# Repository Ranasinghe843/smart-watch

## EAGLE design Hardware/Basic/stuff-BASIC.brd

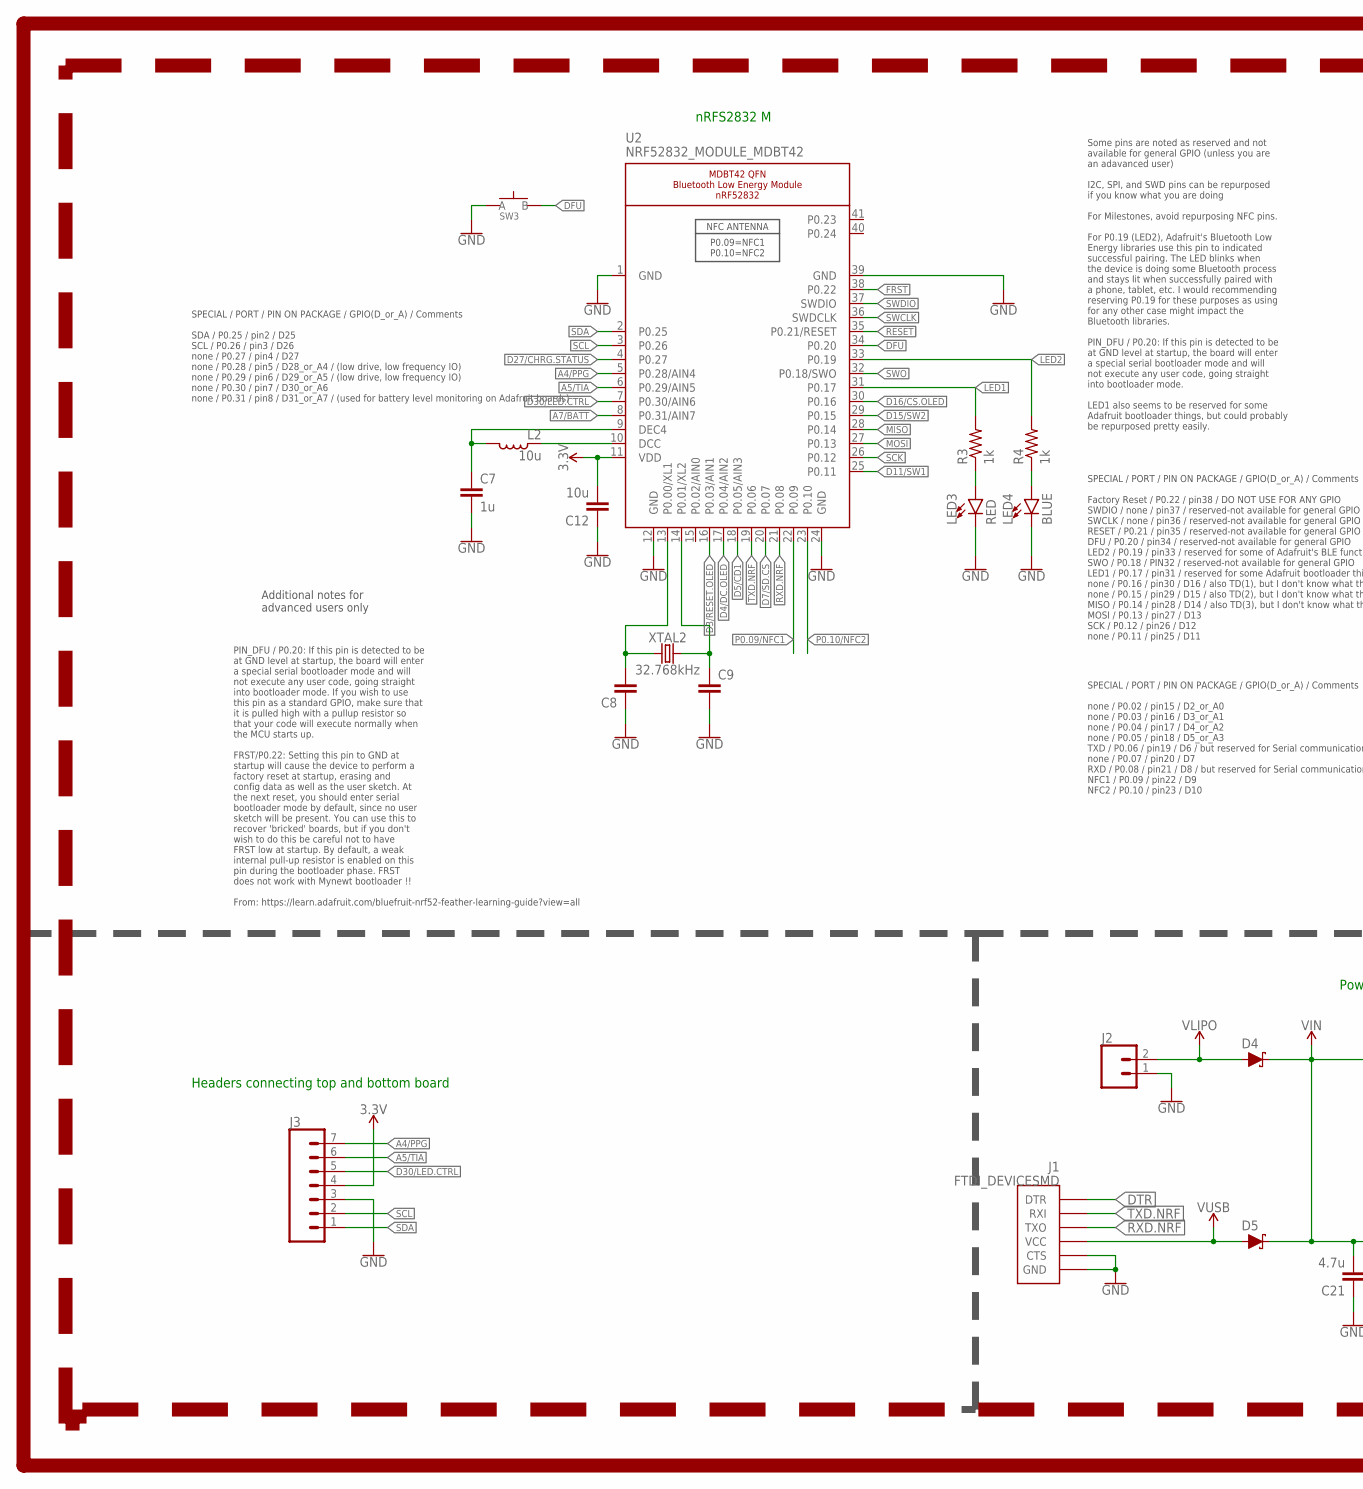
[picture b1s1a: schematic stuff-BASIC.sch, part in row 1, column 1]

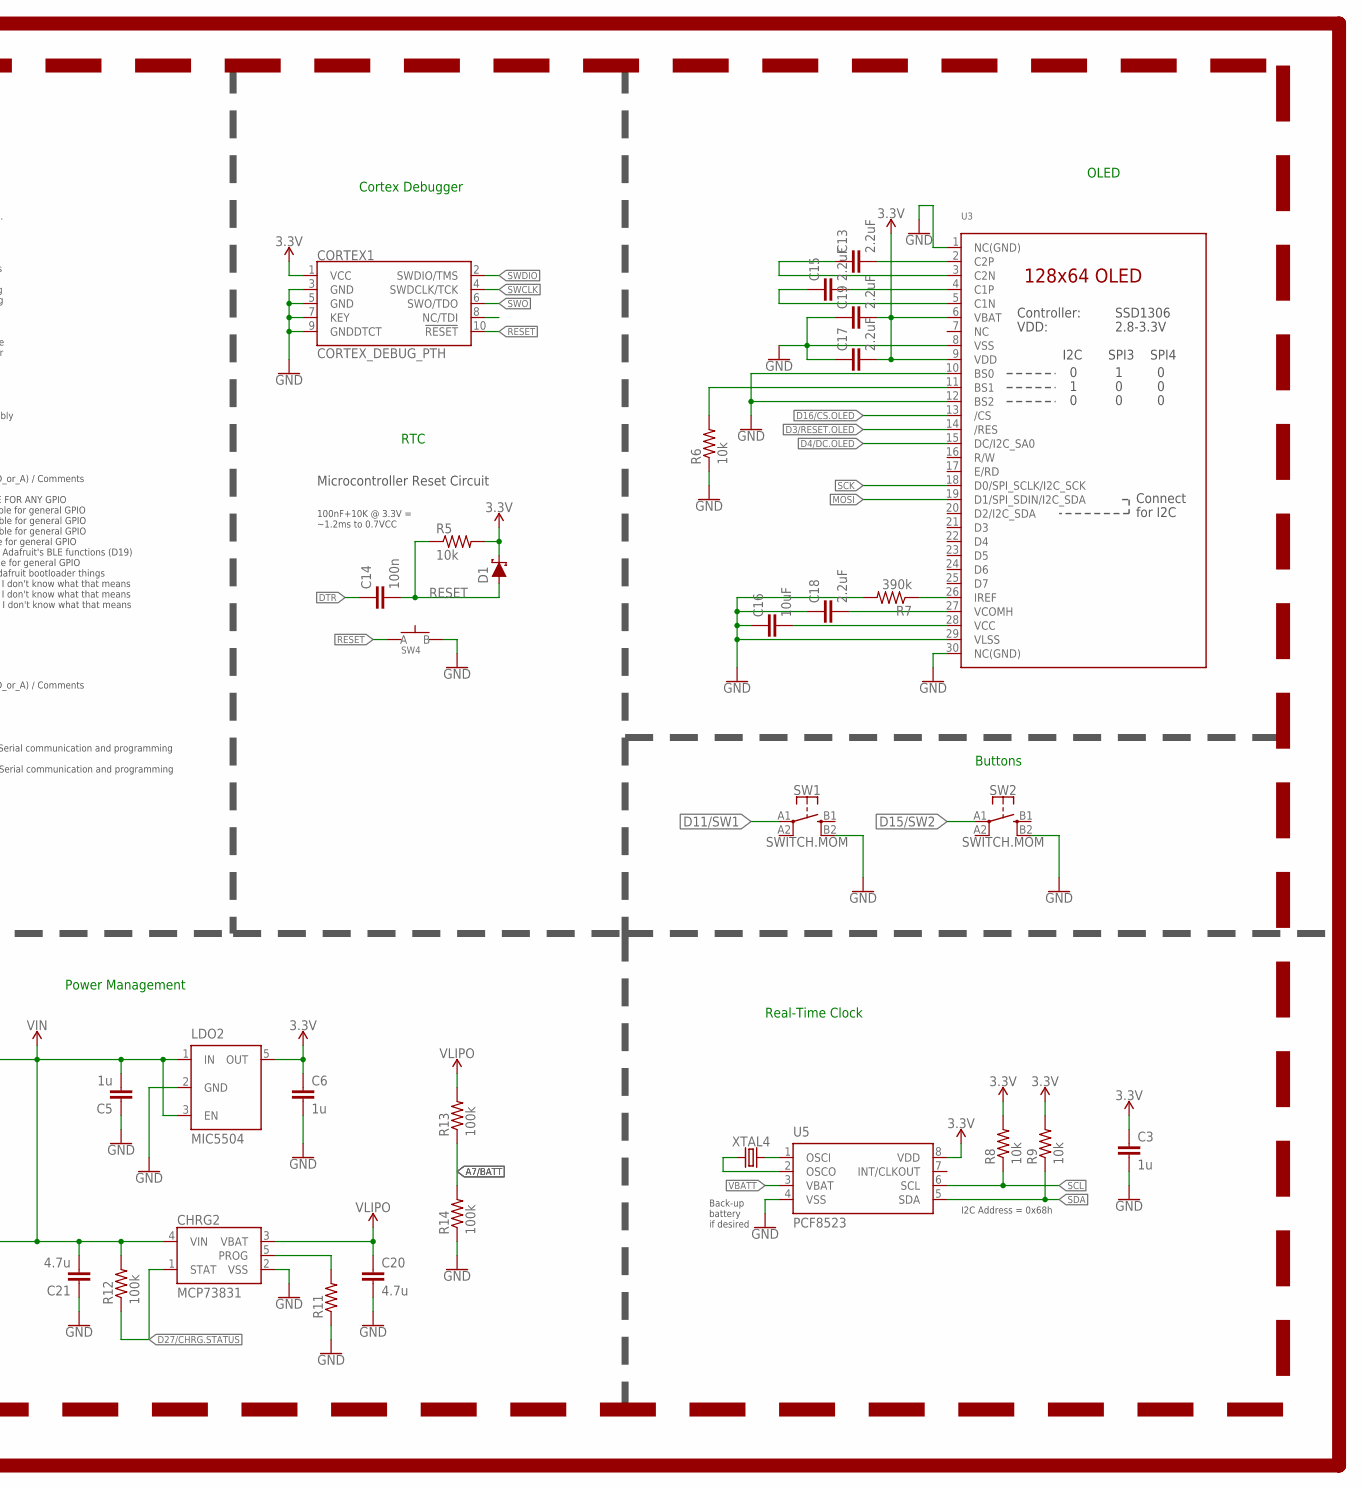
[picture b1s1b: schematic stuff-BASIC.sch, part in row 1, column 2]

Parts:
C3, C5, C6, C7: 1u; C0603
C8, C9: CAPACITOR0603; C0603
C12: 10u; C0805
C13, C15, C17, C18, C19: 2.2uF; C0603
C14: 100n; C0603
C16: 10uF; C0603
C20, C21: 4.7u; C0603
CHRG2: MCP73831; SOT23-5
CORTEX1: CORTEX_DEBUG_PTH; 2X5-PTH-1.27MM
D1, D4, D5: SCHOTTKY-USC; USC
J1: FTDI_DEVICESMD; FTDI-SMD
J2: CONN_02; 1X02
J3: CONN_07-1.27MM; 1X07_1.27MM
L2: 10u; L0603
LDO2: MIC5504; SOT23-5
LED3: RED; LED-0603
LED4: BLUE; LED-0603
R3, R4: 1k; R0603
R5, R6, R8, R9: 10k; R0603
R7: 390k; R0603
R11: RESISTOR0603; R0603
R12, R13, R14: 100k; R0603
SW1, SW2: SWITCH.MOM; TACTILE_SWITCH_SMD_6.2MM_TALL
SW3, SW4: SPST-PTS830GG140-COPY.1-3; BUTTON-GULLWING
U2: NRF52832_MODULE_MDBT42; BLE_MODULE_RAYTAC_MDBT42
U3: DISP_OLED_UG-2864HSWEG01-NO-WRAPAROUND; UG-2864HSWEG01_0.96IN_NO-WRAPAROUND
U5: PCF8523; SO8; DIGIKEY 568-5306-1-ND
XTAL2: 32.768kHz; 2-SMD.NOLEAD.2.0MMTO1.2MM
XTAL4: 32.7680kHz; 2-SMD.NOLEAD.2.0MMTO1.2MM

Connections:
3.3V: C3.1, C6.1, C12.2, C17.2, C19.2, CORTEX1.1 (VCC), D1.- (C), J3.4, LDO2.5 (OUT), R5.2, R8.2, R9.2, U2.11 (VDD), U3.6 (VBAT), U3.9 (VDD), U5.8 (VDD)
A4/PPG: J3.7, U2.5 (P0.28/AIN4)
A5/TIA: J3.6, U2.6 (P0.29/AIN5)
A7/BATT: R13.1, R14.2, U2.8 (P0.31/AIN7)
D3/RESET.OLED: U2.16 (P0.03/AIN1), U3.14 (/RES)
D4/DC.OLED: U2.17 (P0.04/AIN2), U3.15 (DC/I2C_SA0)
D5/CD1: U2.18 (P0.05/AIN3)
D7/SD.CS: U2.20 (P0.07)
D11/SW1: SW1.A1 (1), U2.25 (P0.11)
D15/SW2: SW2.A1 (1), U2.29 (P0.15)
D16/CS.OLED: U2.30 (P0.16), U3.13 (/CS)
D27/CHRG.STATUS: CHRG2.1 (STAT), R12.1, U2.4 (P0.27)
D30/LED.CTRL: J3.5, U2.7 (P0.30/AIN6)
DFU: SW3.3 (B), U2.34 (P0.20)
DTR: C14.1, J1.DTR
FRST: U2.38 (P0.22)
GND: C3.2, C5.1, C6.2, C7.2, C8.1, C9.2, C12.1, C16.1, C17.1, C18.1, C19.1, C20.2, C21.1, CHRG2.2 (VSS), CORTEX1.3 (GND), CORTEX1.5 (GND), CORTEX1.7 (KEY), CORTEX1.9 (GNDDTCT), J1.CTS, J1.GND, J2.1, J3.3, LDO2.2 (GND), LED3.C, LED4.C, R6.1, R7.2, R11.1, R14.1, SW1.B2 (4), SW2.B2 (4), SW3.1 (A), SW4.3 (B), U2.1 (GND), U2.12 (GND), U2.24 (GND), U2.39 (GND), U3.1 (NC(GND)), U3.8 (VSS), U3.10 (BS0), U3.12 (BS2), U3.29 (VLSS), U3.30 (NC(GND)), U5.4 (VSS)
LED1: R3.2, U2.31 (P0.17)
LED2: R4.2, U2.33 (P0.19)
MISO: U2.28 (P0.14)
MOSI: U2.27 (P0.13), U3.19 (D1/SPI_SDIN/I2C_SDA)
unnamed: R6.2, U3.11 (BS1)
unnamed: R7.1, U3.26 (IREF)
unnamed: C13.2, U3.2 (C2P)
unnamed: C8.2, U2.13 (P0.00/XL1), XTAL2.P$1 (1)
unnamed: C13.1, U3.3 (C2N)
unnamed: C9.1, U2.14 (P0.01/XL2), XTAL2.P$2 (2)
unnamed: C15.2, U3.4 (C1P)
unnamed: C15.1, U3.5 (C1N)
unnamed: LED3.A, R3.1
unnamed: LED4.A, R4.1
unnamed: L2.1, U2.10 (DCC)
unnamed: C7.1, L2.2, U2.9 (DEC4)
unnamed: C16.2, U3.28 (VCC)
unnamed: C18.2, U3.27 (VCOMH)
unnamed: CHRG2.5 (PROG), R11.2
unnamed: U5.2 (OSCO), XTAL4.P$1 (1)
unnamed: U5.1 (OSCI), XTAL4.P$2 (2)
P0.09/NFC1: U2.22 (P0.09)
P0.10/NFC2: U2.23 (P0.10)
RESET: C14.2, CORTEX1.10 (!RESET), D1.+ (A), R5.1, SW4.1 (A), U2.35 (P0.21/RESET)
RXD.NRF: J1.TXO, U2.21 (P0.08)
SCK: U2.26 (P0.12), U3.18 (D0/SPI_SCLK/I2C_SCK)
SCL: J3.2, R8.1, U2.3 (P0.26), U5.6 (SCL)
SDA: J3.1, R9.1, U2.2 (P0.25), U5.5 (SDA)
SWCLK: CORTEX1.4 (SWDCLK/TCK), U2.36 (SWDCLK)
SWDIO: CORTEX1.2 (SWDIO/TMS), U2.37 (SWDIO)
SWO: CORTEX1.6 (SWO/TDO), U2.32 (P0.18/SWO)
TXD.NRF: J1.RXI, U2.19 (P0.06)
VBATT: U5.3 (VBAT)
VIN: C5.2, C21.2, CHRG2.4 (VIN), D4.- (C), D5.- (C), LDO2.1 (IN), LDO2.3 (EN), R12.2
VLIPO: C20.1, CHRG2.3 (VBAT), D4.+ (A), J2.2, R13.2
V_USB: D5.+ (A), J1.VCC

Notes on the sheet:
Microcontroller Reset Circuit
100nF+10K @ 3.3V = ~1.2ms to 0.7VCC
SPECIAL / PORT / PIN ON PACKAGE / GPIO(D_or_A) / Comments SDA / P0.25 / pin2 / D25 SCL / P0.26 / pin3 / D26 none / P0.27 / pin4 / D27 none / P0.28 / pin5 / D28_or_A4 / (low drive, low frequency IO) none / P0.29 / pin6 / D29_or_A5 / (low drive, low frequency IO) none / P0.30 / pin7 / D30_or_A6 none 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
SPECIAL / PORT / PIN ON PACKAGE / GPIO(D_or_A) / Comments none / P0.02 / pin15 / D2_or_A0 none / P0.03 / pin16 / D3_or_A1 none / P0.04 / pin17 / D4_or_A2 none / P0.05 / pin18 / D5_or_A3 TXD / P0.06 / pin19 / D6 / but reserved for Serial communication and programming none / P0.07 / pin20 / D7 RXD / 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
SPECIAL / PORT / PIN ON PACKAGE / GPIO(D_or_A) / Comments Factory Reset / P0.22 / pin38 / DO NOT USE FOR ANY GPIO SWDIO / none / pin37 / reserved-not available for general GPIO SWCLK / none / pin36 / reserved-not available for general GPIO RESET / P0.21 / pin35 / reserved-not available for general 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
Some pins are noted as reserved and not available for general GPIO (unless you are an adavanced user) I2C, SPI, and SWD pins can be repurposed if you know what you are doing For Milestones, avoid repurposing NFC pins. For P0.19 (LED2), Adafruit's Bluetooth Low Energy libraries use this pin to indic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
PIN_DFU / P0.20: If this pin is detected to be at GND level at startup, the board will enter a special serial bootloader mode and will not execute any user code, going straight into bootloader mode. If you wish to use this pin as a standard GPIO, make sure that it is pulled high with a pullup resis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
Additional notes for advanced users only
nRFS2832 M
OLED
Power Management
Buttons
Real-Time Clock
Cortex Debugger
RTC
Headers connecting top and bottom board
I2C Address = 0x68h
Back-up battery if desired

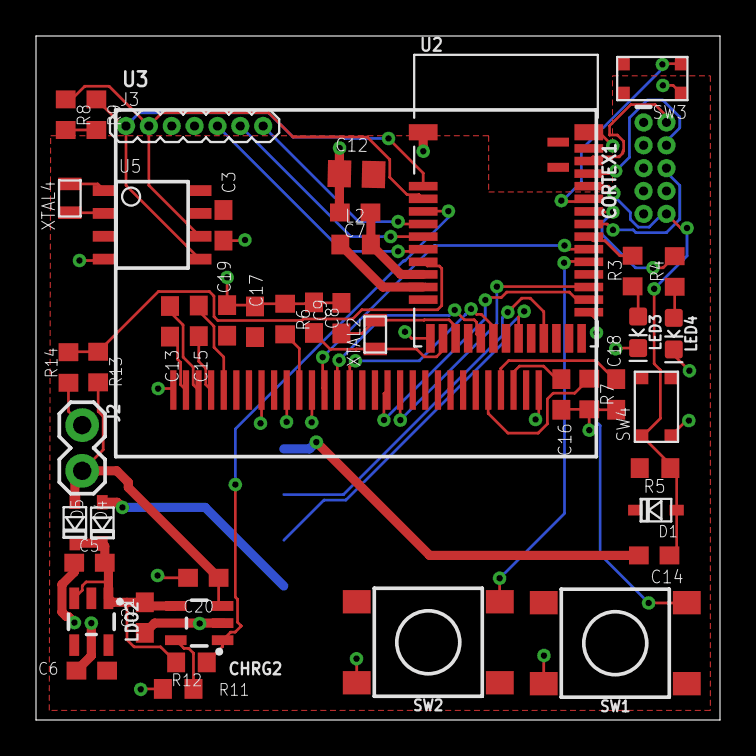
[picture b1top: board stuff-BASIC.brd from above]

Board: 2 copper layers, 38.0 x 38.0 mm, 48 parts (1 on the bottom side), 46 nets.

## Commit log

2022-09-14 Initial Organization
2022-09-15 Half Done Schematic
2022-09-22 done until 22 min mark
2022-10-05 Complete arduino video and add header
2022-10-05 fixed inconsistency errors
2022-10-05 Complete schematic
2022-10-06 Start organizing and routing
2022-10-19 Airwires
